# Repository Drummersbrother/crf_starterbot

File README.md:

# crf_starterbot
A robotics starter kit/bot based on the https://github.com/ideaHex/FHTbot/, for Chalmers Robotförening https://chalmersrobotics.se/

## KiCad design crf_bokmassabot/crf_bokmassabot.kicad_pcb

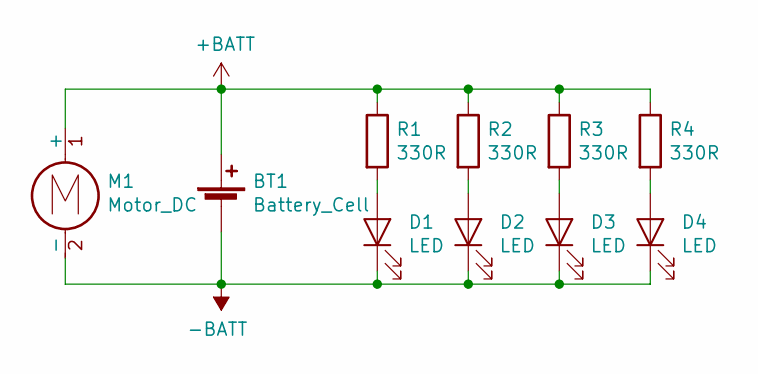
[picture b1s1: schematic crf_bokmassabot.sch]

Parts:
BT1: Battery_Cell; BatteryHolder_LINX_BAT-HLD-012-SMT
D1, D2, D3, D4: LED; LED_D3.0mm
M1: Motor_DC; D_1812_4532Metric
R1, R2, R3, R4: 330R; R_0603_1608Metric

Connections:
+BATT: BT1.1 (+), M1.1 (+), R1.1, R2.1, R3.1, R4.1
-BATT: BT1.2 (-), D1.1 (K), D2.1 (K), D3.1 (K), D4.1 (K), M1.2 (-)
unnamed: D1.2 (A), R1.2
unnamed: D2.2 (A), R2.2
unnamed: D3.2 (A), R3.2
unnamed: D4.2 (A), R4.2

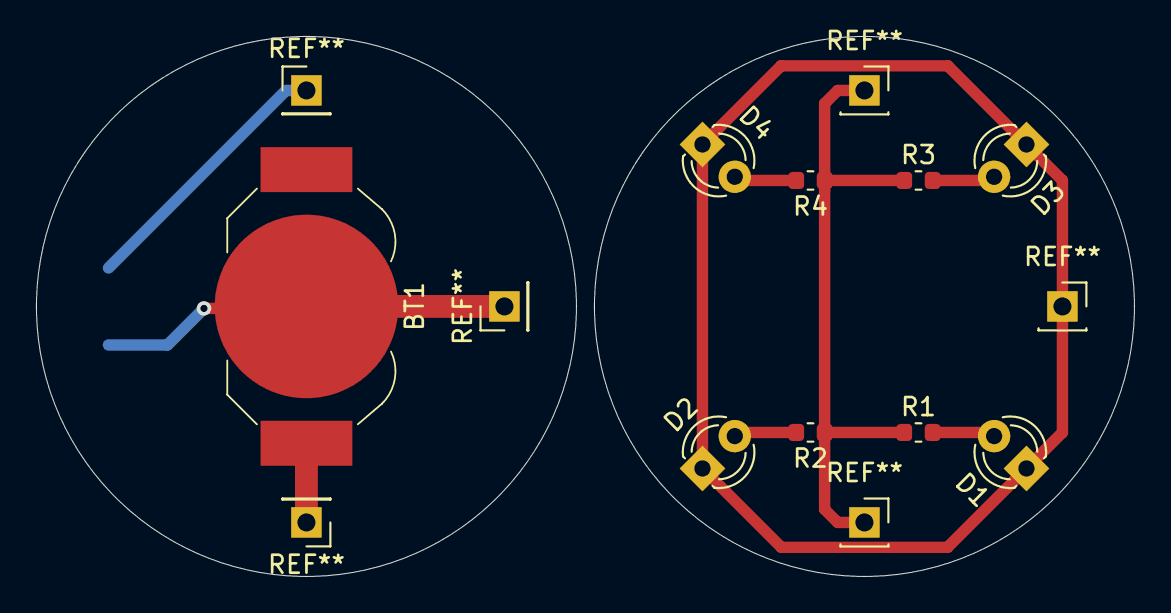
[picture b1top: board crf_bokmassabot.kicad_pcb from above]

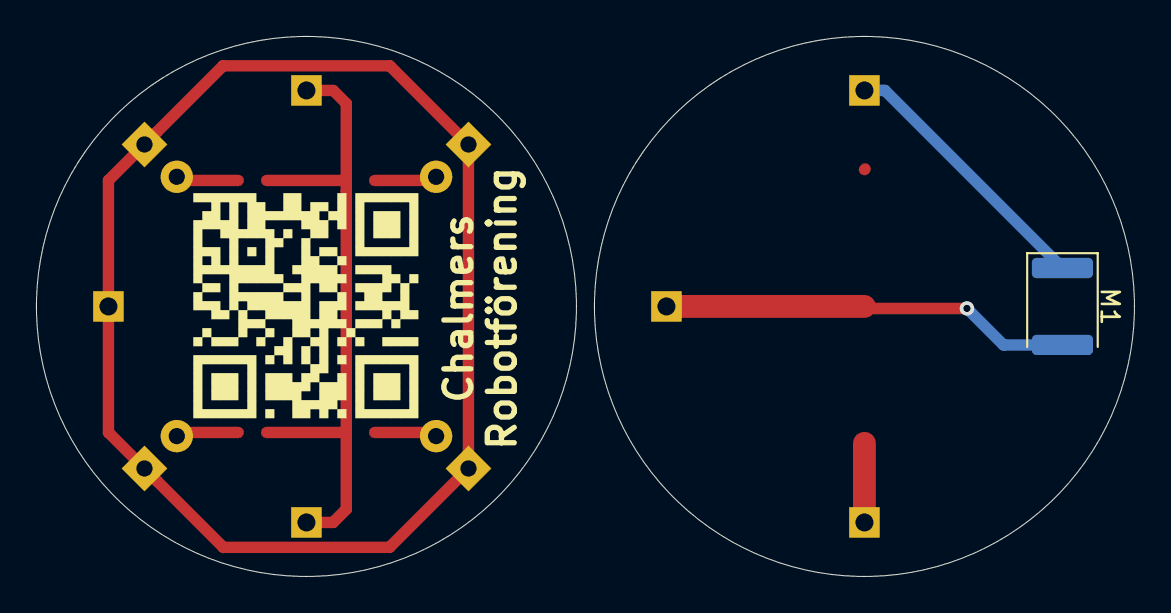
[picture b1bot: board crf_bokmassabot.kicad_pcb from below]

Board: 2 copper layers, 61.0 x 30.0 mm, 11 parts (2 on the bottom side), 6 nets.

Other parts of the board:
LOGO: LOGO

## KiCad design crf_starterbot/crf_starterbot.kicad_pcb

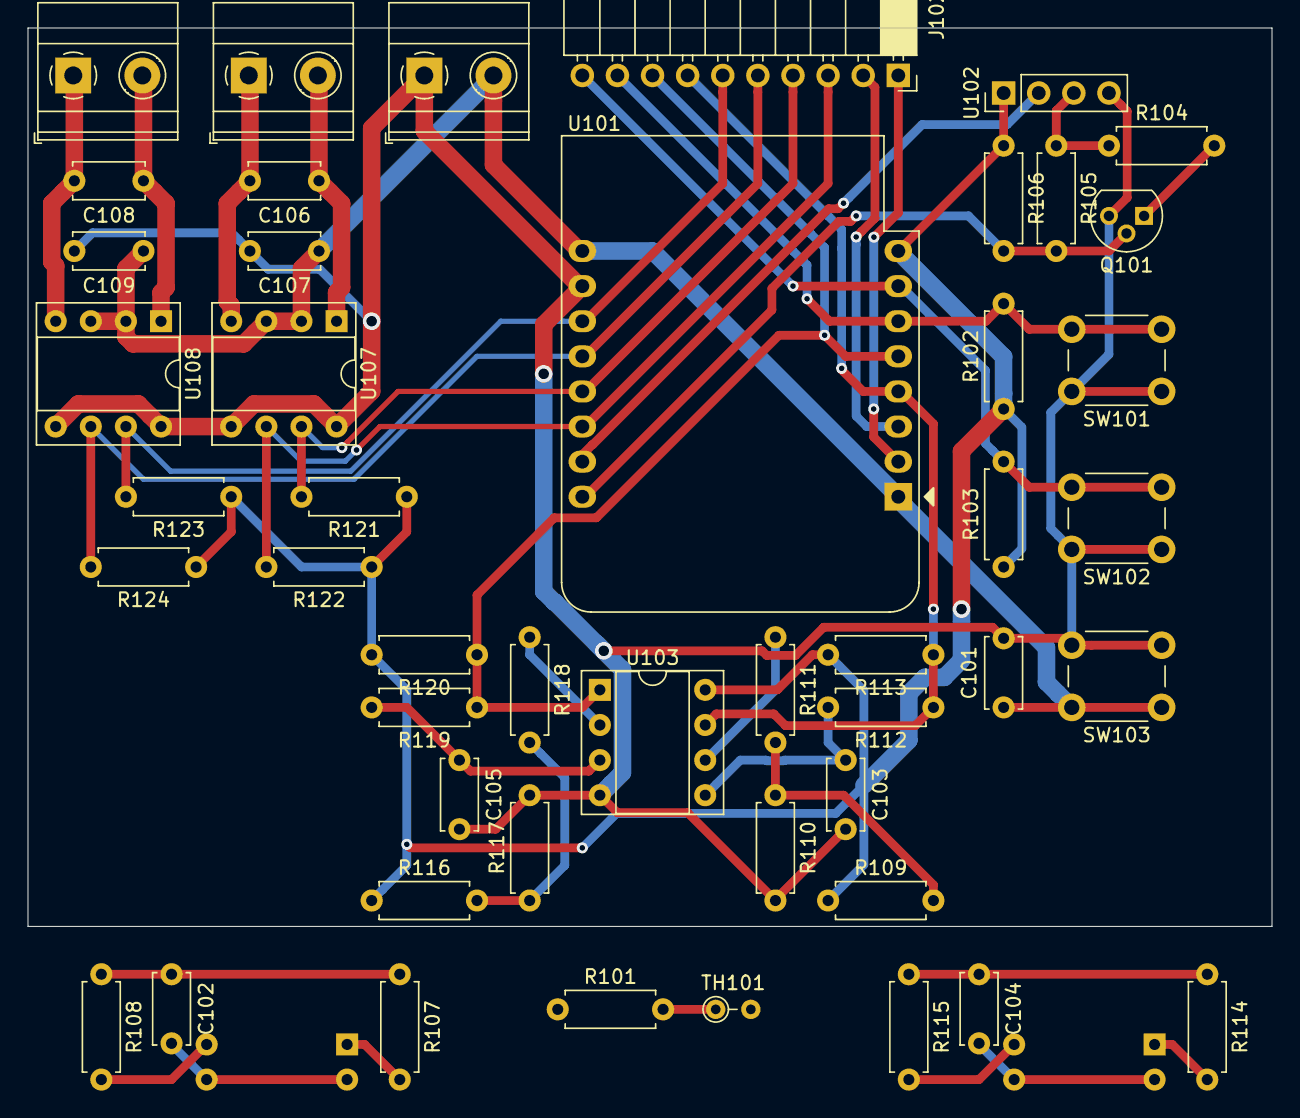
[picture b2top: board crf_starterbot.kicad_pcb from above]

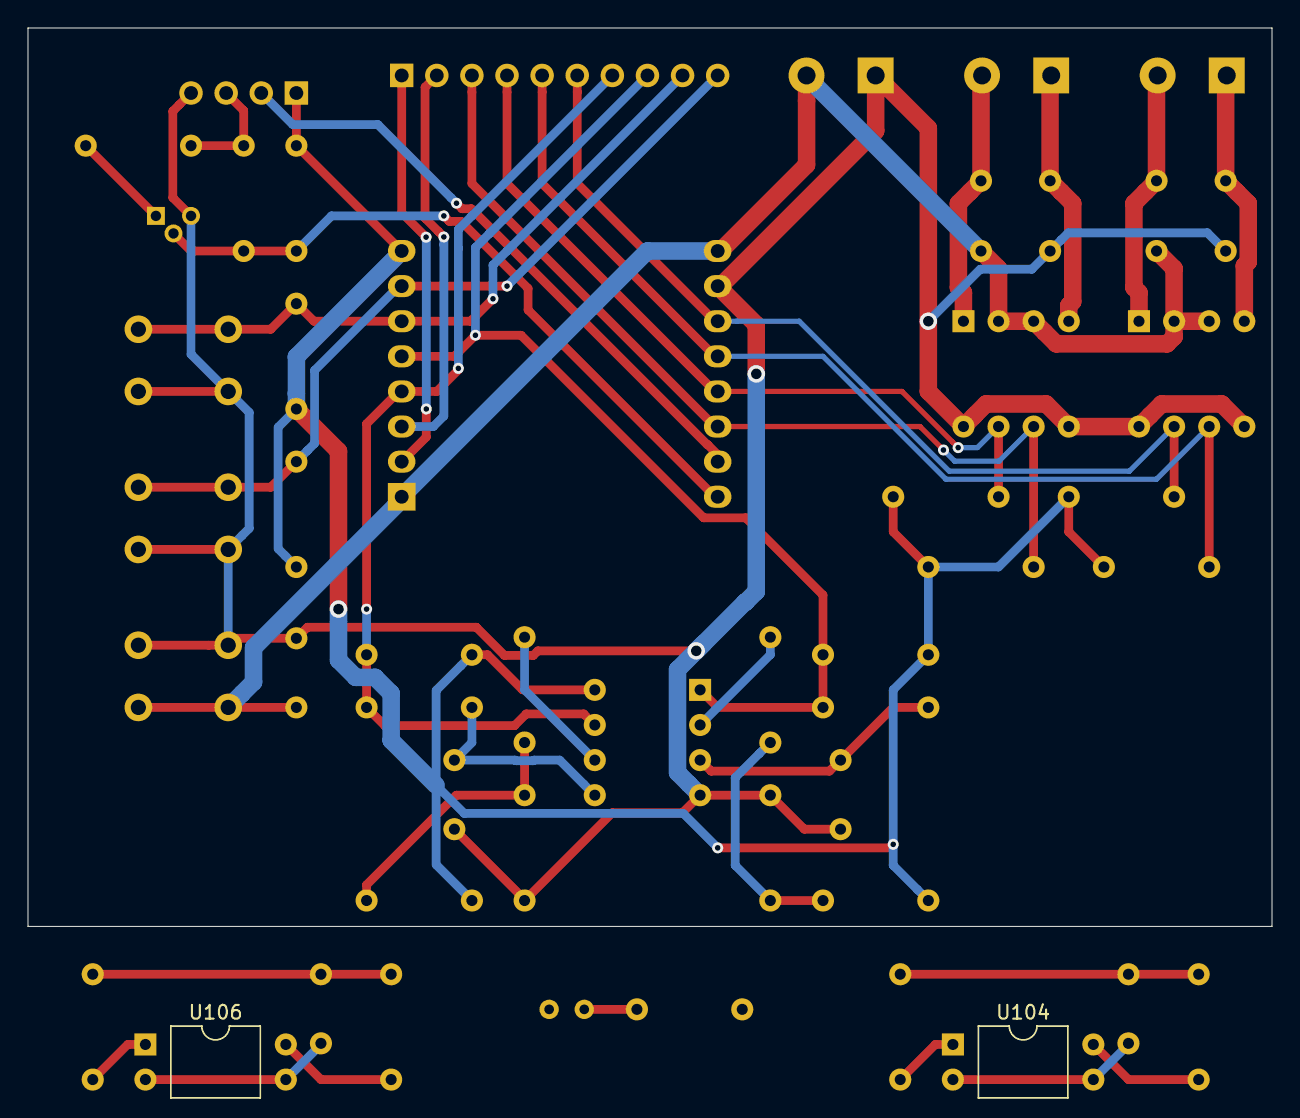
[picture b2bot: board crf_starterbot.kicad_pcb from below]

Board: 2 copper layers, 90.0 x 65.0 mm, 49 parts (2 on the bottom side), 29 nets.

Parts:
C101: 10n; C_Disc_D5.0mm_W2.5mm_P5.00mm
C102, C103, C104, C105, C106, C107, C108, C109: 100n; C_Disc_D5.0mm_W2.5mm_P5.00mm
J101, J103, J104: Screw_Terminal_01x02; TerminalBlock_Phoenix_MKDS-1,5-2_1x02_P5.00mm_Horizontal
J102: Conn_01x10_Female; PinSocket_1x10_P2.54mm_Horizontal
Q101: Q_NPN_BCE; TO-92
R101: 33K; R_Axial_DIN0207_L6.3mm_D2.5mm_P7.62mm_Horizontal
R102, R103: 10K; R_Axial_DIN0207_L6.3mm_D2.5mm_P7.62mm_Horizontal
R104, R106: DNL/100K; R_Axial_DIN0207_L6.3mm_D2.5mm_P7.62mm_Horizontal
R105: 0; R_Axial_DIN0207_L6.3mm_D2.5mm_P7.62mm_Horizontal
R107, R114: 180R; R_Axial_DIN0207_L6.3mm_D2.5mm_P7.62mm_Horizontal
R108, R109, R110, R111, R113, R115, R116, R117, R118, R120, R121, R122, R123, R124: 10k; R_Axial_DIN0207_L6.3mm_D2.5mm_P7.62mm_Horizontal
R112, R119: 100k; R_Axial_DIN0207_L6.3mm_D2.5mm_P7.62mm_Horizontal
SW101, SW102, SW103: SW_SPST; SW_PUSH_6mm
TH101: Thermistor_NTC; R_Axial_DIN0204_L3.6mm_D1.6mm_P2.54mm_Vertical
U101: WeMos_D1_mini; WEMOS_D1_mini_light
U102: HC-SR04; PinHeader_1x04_P2.54mm_Vertical
U103: LM393; DIP-8_W7.62mm_Socket
U104, U106: E048-03; DIP-4_W10.16mm
U107, U108: L9110; DIP-8_W7.62mm_Socket

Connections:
+3V3: C102.1, C104.1, R101.1, R102.1, R103.1, R106.1, R107.1, R108.1, R109.1, R113.2, R114.1, R115.1, R116.1, R120.2, R121.1, R122.1, R123.1, R124.1, U101.8, U102.1, U103.8
+BATT: C101.1, C107.1, C109.1, J101.2, SW103.1, U101.1, U101.9, U107.2, U107.3, U108.2, U108.3
ECHO: Q101.2, R105.2, R106.2, U101.16
GND: C101.2, C102.2, C103.2, C104.2, C105.2, C107.2, C109.2, J101.1, Q101.3, R110.2, R117.2, SW101.1, SW102.1, SW103.2, TH101.2, U101.10, U102.4, U103.4, U104.2, U104.3, U106.2, U106.3, U107.5, U107.8, U108.5, U108.8
LEFTA: J102.3, R122.2, U101.14, U107.6
LEFTB: J102.4, R121.2, U101.13, U107.7
LEFT_ENC: J102.7, R112.1, R113.1, U101.4, U103.7
LEFT_SW: J102.9, R102.2, SW101.2, U101.6
unnamed: C103.1, R108.2, R112.2, U103.5, U104.4
unnamed: C105.1, R115.2, R119.2, U103.3, U106.4
unnamed: C106.1, J103.2, U107.1
unnamed: C106.2, J103.1, U107.4
unnamed: C108.1, J104.2, U108.1
unnamed: C108.2, J104.1, U108.4
unnamed: J102.2, U101.3
unnamed: Q101.1, R104.2
unnamed: R104.1, R105.1, U102.3
unnamed: R107.2, U104.1
unnamed: R109.2, R110.1, R111.2
unnamed: R111.1, U103.6
unnamed: R114.2, U106.1
unnamed: R116.2, R117.1, R118.2
unnamed: R118.1, U103.2
RIGHTA: J102.5, R124.2, U101.12, U108.6
RIGHTB: J102.6, R123.2, U101.11, U108.7
RIGHT_ENC: J102.8, R119.1, R120.1, U101.5, U103.1
RIGHT_SW: J102.10, R103.2, SW102.2, U101.7
TEMP: J102.1, R101.2, TH101.1, U101.2
TRIG: U101.15, U102.2

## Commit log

2019-08-28 Added the FHTbot schematic
2019-09-01 Begun kicad project file
2019-09-02 Begun importing components
2019-09-03 Continued importing from the given schematic
2019-09-03 Almost completed all essential circuits
2019-09-04 basically finished the schematic
2019-09-05 Started layout considerations of the pcb
2019-09-10 Completed placement of components into functional units, begun routing
2019-09-10 State of board before proper placement of phototransistors and interconnection functional units
2019-09-10 Completed routing of all components except thermistor and phototransistors, need to discuss those with robert
2019-09-15 Completed a first draft of bot for bokmässan
2019-09-18 Fixed a bug causing the motor to be on at any time when the battery is in the holder
2019-09-19 Added fabrication outputs, BOM is todo
